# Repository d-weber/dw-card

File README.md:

# My business card

### Features:
- ESP32-S3
- 240x240 TFT LCD
- 8 Buttons
- Battery (CR2032) or USB-C Powered
- Cladd D Audio amp with 1W Speaker

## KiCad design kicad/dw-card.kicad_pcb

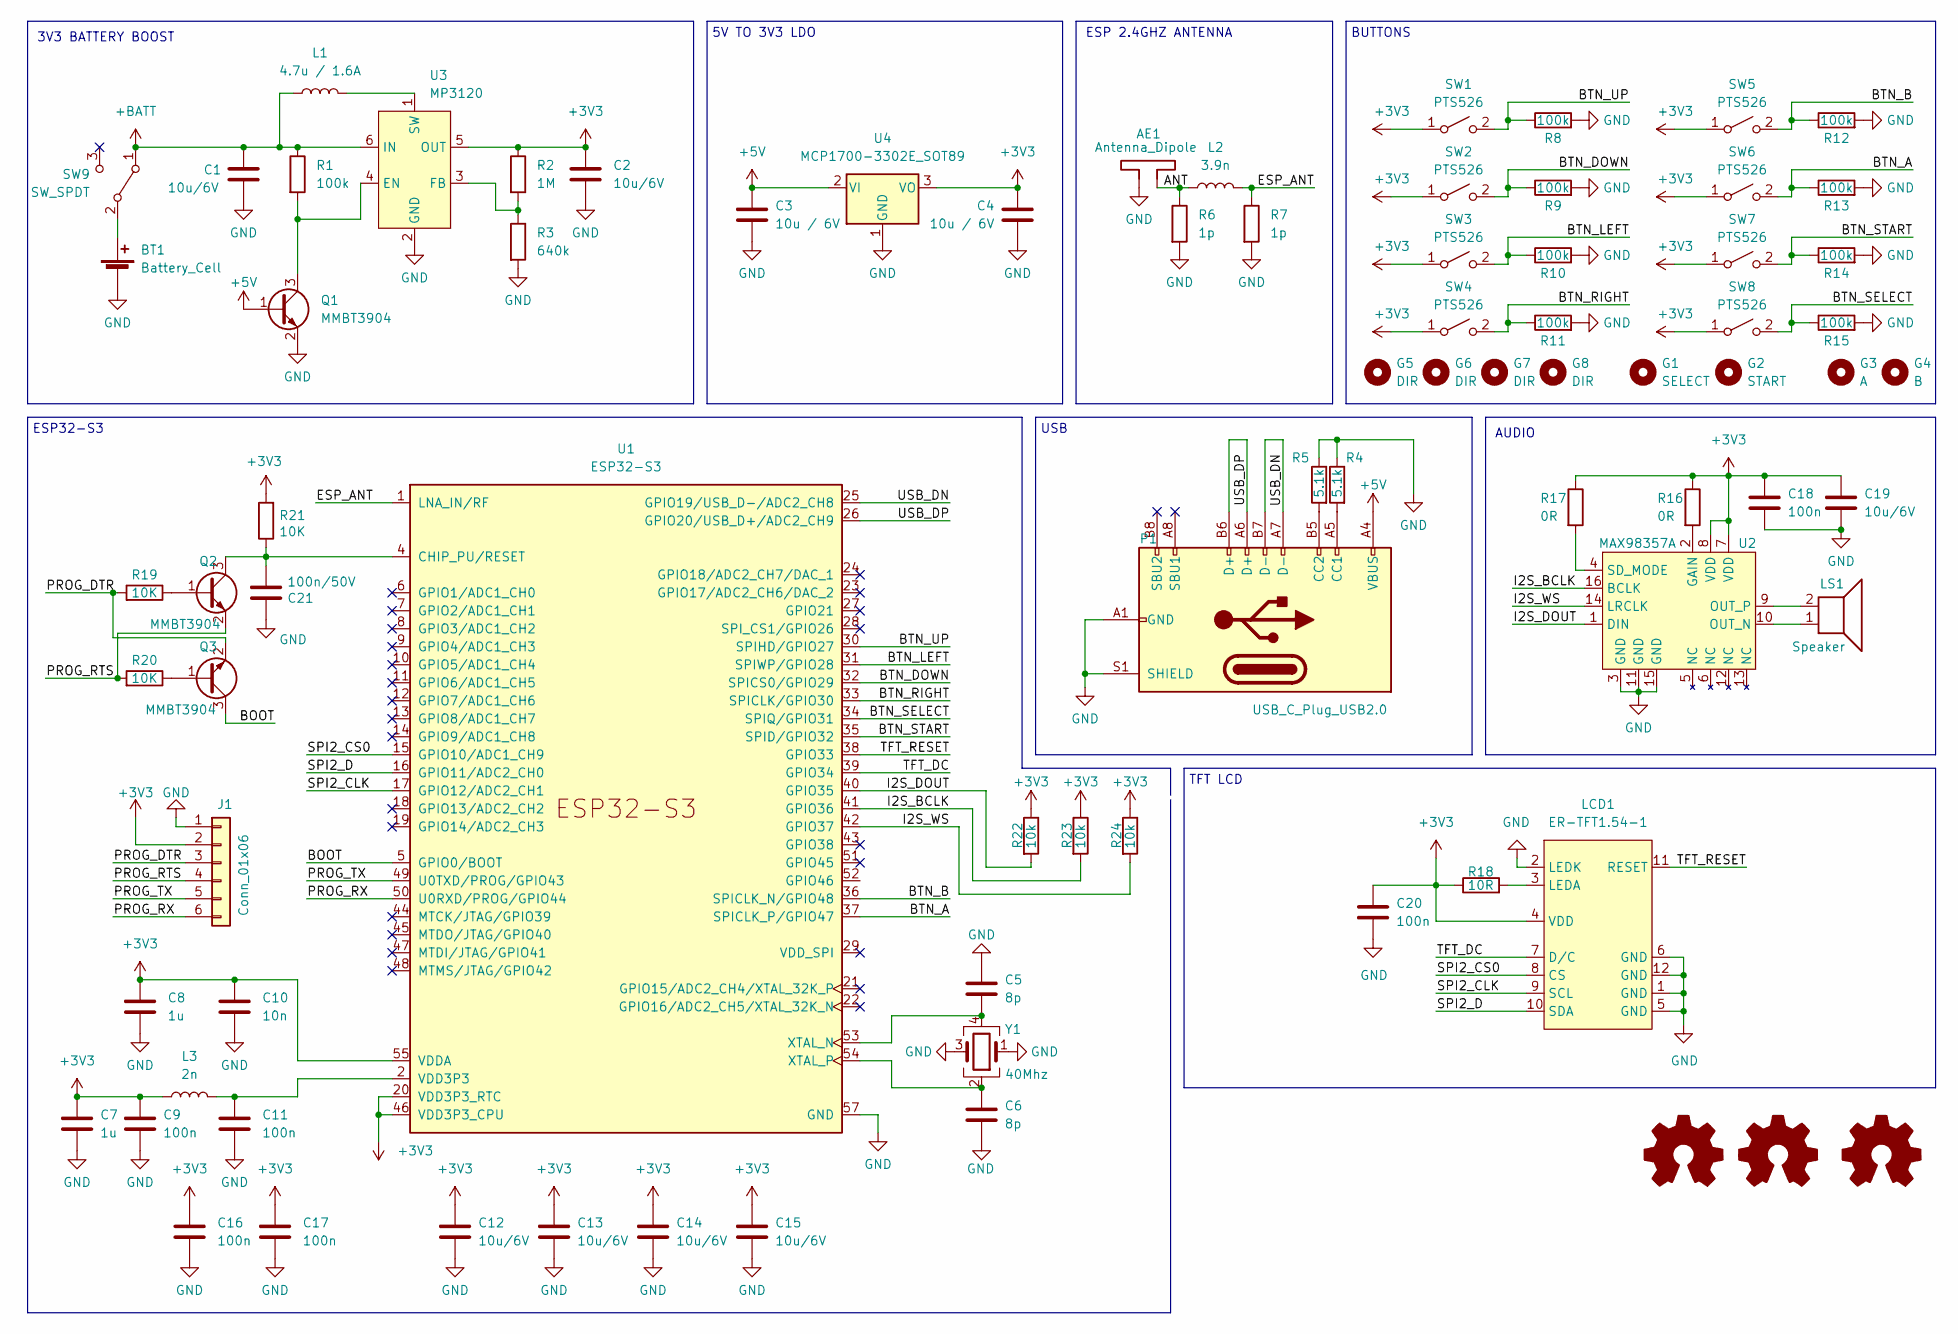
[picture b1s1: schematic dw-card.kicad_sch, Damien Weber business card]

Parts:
AE1: Antenna_Dipole; SWRA117D_Right
BT1: Battery_Cell; 2980
C1, C2, C12, C13, C14, C15, C19: 10u/6V; C_0805_2012Metric
C3, C4: 10u / 6V; C_0805_2012Metric
C5, C6: 8p; C_0603_1608Metric
C7, C8: 1u; C_0603_1608Metric
C9, C11, C16, C17, C18, C20: 100n; C_0603_1608Metric
C10: 10n; C_0603_1608Metric
C21: 100n/50V; C_0603_1608Metric
G1: SELECT; btn_select
G2: START; btn_start
G3: A; btn_a
G4: B; btn_b
G5, G6, G7, G8: DIR; btn_dir
J1: Conn_01x06; TC2030-MCP-NL
L1: 4.7u / 1.6A; L_Taiyo-Yuden_MD-3030
L2: 3.9n; L_0402_1005Metric
L3: 2n; L_0603_1608Metric
LCD1: ER-TFT1.54-1; ER-TFT-1.54
LDW1: Logo_Open_Hardware_Small; logo
LDW2: Logo_Open_Hardware_Small; logo_dw
LDW3: Logo_Open_Hardware_Small; qrcode_github
LS1: Speaker; CMS-15118D-SP
P1: USB_C_Plug_USB2.0; USB4510
Q1, Q2, Q3: MMBT3904; SOT-23
R1, R8, R9, R10, R11, R12, R13, R14, R15: 100k; R_0603_1608Metric
R2: 1M; R_0603_1608Metric
R3: 640k; R_0603_1608Metric
R4, R5: 5.1k; R_0603_1608Metric
R6, R7: 1p; R_0402_1005Metric
R16, R17: 0R; R_0603_1608Metric
R18: 10R; R_0603_1608Metric
R19, R20, R21: 10K; R_0603_1608Metric
R22, R23, R24: 10k; R_0603_1608Metric
SW1, SW2, SW3, SW4, SW5, SW6, SW7, SW8: PTS526
SW9: SW_SPDT; SW_SPDT_PCM12
U1: ESP32-S3; QFN-56-1EP_7x7mm_P0.4mm_EP5.6x5.6mm
U2: MAX98357A; TQFN-16-1EP_3x3mm_P0.5mm_EP1.23x1.23mm
U3: MP3120; TSOT-23-6
U4: MCP1700-3302E_SOT89; SOT-89-3
Y1: 40Mhz; Crystal_SMD_2016-4Pin_2.0x1.6mm

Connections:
+3V3: C2.1, C4.2, C7.1, C8.1, C9.1, C10.1, C12.1, C13.1, C14.1, C15.1, C16.1, C17.1, C18.1, C19.1, C20.1, J1.2, L3.1, LCD1.4 (VDD), R2.1, R16.1, R17.1, R18.1, R21.2, R22.1, R23.1, R24.1, SW1.1 (A), SW2.1 (A), SW3.1 (A), SW4.1 (A), SW5.1 (A), SW6.1 (A), SW7.1 (A), SW8.1 (A), U1.20 (VDD3P3_RTC), U1.46 (VDD3P3_CPU), U1.55 (VDDA), U1.56 (VDDA), U2.7 (VDD), U2.8 (VDD), U3.5 (OUT), U4.3 (VO)
+5V: C3.1, P1.A4 (VBUS), P1.A9 (VBUS), Q1.1 (B), U4.2 (VI)
+BATT: C1.1, L1.1, R1.1, SW9.1 (A), U3.6 (IN)
/ANT: AE1.1, L2.1, R6.1
/BOOT: Q3.3 (C), U1.5 (GPIO0/BOOT)
/BTN_A: R13.1, SW6.2 (B), U1.37 (SPICLK_P/GPIO47)
/BTN_B: R12.1, SW5.2 (B), U1.36 (SPICLK_N/GPIO48)
/BTN_DOWN: R9.1, SW2.2 (B), U1.32 (SPICS0/GPIO29)
/BTN_LEFT: R10.1, SW3.2 (B), U1.31 (SPIWP/GPIO28)
/BTN_RIGHT: R11.1, SW4.2 (B), U1.33 (SPICLK/GPIO30)
/BTN_SELECT: R15.1, SW8.2 (B), U1.34 (SPIQ/GPIO31)
/BTN_START: R14.1, SW7.2 (B), U1.35 (SPID/GPIO32)
/BTN_UP: R8.1, SW1.2 (B), U1.30 (SPIHD/GPIO27)
/ESP_ANT: L2.2, R7.1, U1.1 (LNA_IN/RF)
/I2S_BCLK: R23.2, U1.41 (GPIO36), U2.16 (BCLK)
/I2S_DOUT: R22.2, U1.40 (GPIO35), U2.1 (DIN)
/I2S_WS: R24.2, U1.42 (GPIO37), U2.14 (LRCLK)
/PROG_DTR: J1.3, Q3.2 (E), R19.2
/PROG_RTS: J1.4, Q2.2 (E), R20.2
/PROG_RX: J1.6, U1.50 (U0RXD/PROG/GPIO44)
/PROG_TX: J1.5, U1.49 (U0TXD/PROG/GPIO43)
/SPI2_CLK: LCD1.9 (SCL), U1.17 (GPIO12/ADC2_CH1)
/SPI2_CS0: LCD1.8 (CS), U1.15 (GPIO10/ADC1_CH9)
/SPI2_D: LCD1.10 (SDA), U1.16 (GPIO11/ADC2_CH0)
/TFT_DC: LCD1.7 (D/C), U1.39 (GPIO34)
/TFT_RESET: LCD1.11 (RESET), U1.38 (GPIO33)
/USB_DN: P1.A7 (D-), P1.B7 (D-), U1.25 (GPIO19/USB_D-/ADC2_CH8)
/USB_DP: P1.A6 (D+), P1.B6 (D+), U1.26 (GPIO20/USB_D+/ADC2_CH9)
GND: AE1.2, BT1.2 (-), C1.2, C2.2, C3.2, C4.1, C5.1, C6.2, C7.2, C8.2, C9.2, C10.2, C11.2, C12.2, C13.2, C14.2, C15.2, C16.2, C17.2, C18.2, C19.2, C20.2, C21.2, J1.1, LCD1.1 (GND), LCD1.2 (LEDK), LCD1.5 (GND), LCD1.6 (GND), LCD1.12 (GND), P1.A1 (GND), P1.A12 (GND), P1.S1 (SHIELD), Q1.2 (E), R3.2, R4.1, R5.1, R6.2, R7.2, R8.2, R9.2, R10.2, R11.2, R12.2, R13.2, R14.2, R15.2, U1.57 (GND), U2.3 (GND), U2.11 (GND), U2.15 (GND), U3.2 (GND), U4.1 (GND), Y1.1, Y1.3
unnamed: BT1.1 (+), SW9.2 (B)
unnamed: LCD1.3 (LEDA), R18.2
unnamed: P1.A5 (CC1), R4.2
unnamed: P1.B5 (CC2), R5.2
unnamed: Q1.3 (C), R1.2, U3.4 (EN)
unnamed: Q2.1 (B), R19.1
unnamed: C21.1, Q2.3 (C), R21.1, U1.4 (CHIP_PU/RESET)
unnamed: Q3.1 (B), R20.1
unnamed: C5.2, U1.53 (XTAL_N), Y1.4
unnamed: C6.1, U1.54 (XTAL_P), Y1.2
unnamed: R16.2, U2.2 (GAIN)
unnamed: LS1.1, U2.10 (OUT_N)
unnamed: LS1.2, U2.9 (OUT_P)
unnamed: R17.2, U2.4 (SD_MODE)
unnamed: R2.2, R3.1, U3.3 (FB)
unnamed: L1.2, U3.1 (SW)
VDD3P3: C11.1, L3.2, U1.2 (VDD3P3), U1.3 (VDD3P3)

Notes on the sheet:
ESP32-S3
BUTTONS
AUDIO
ESP 2.4GHZ ANTENNA
5V TO 3V3 LDO
TFT LCD
USB
3V3 BATTERY BOOST

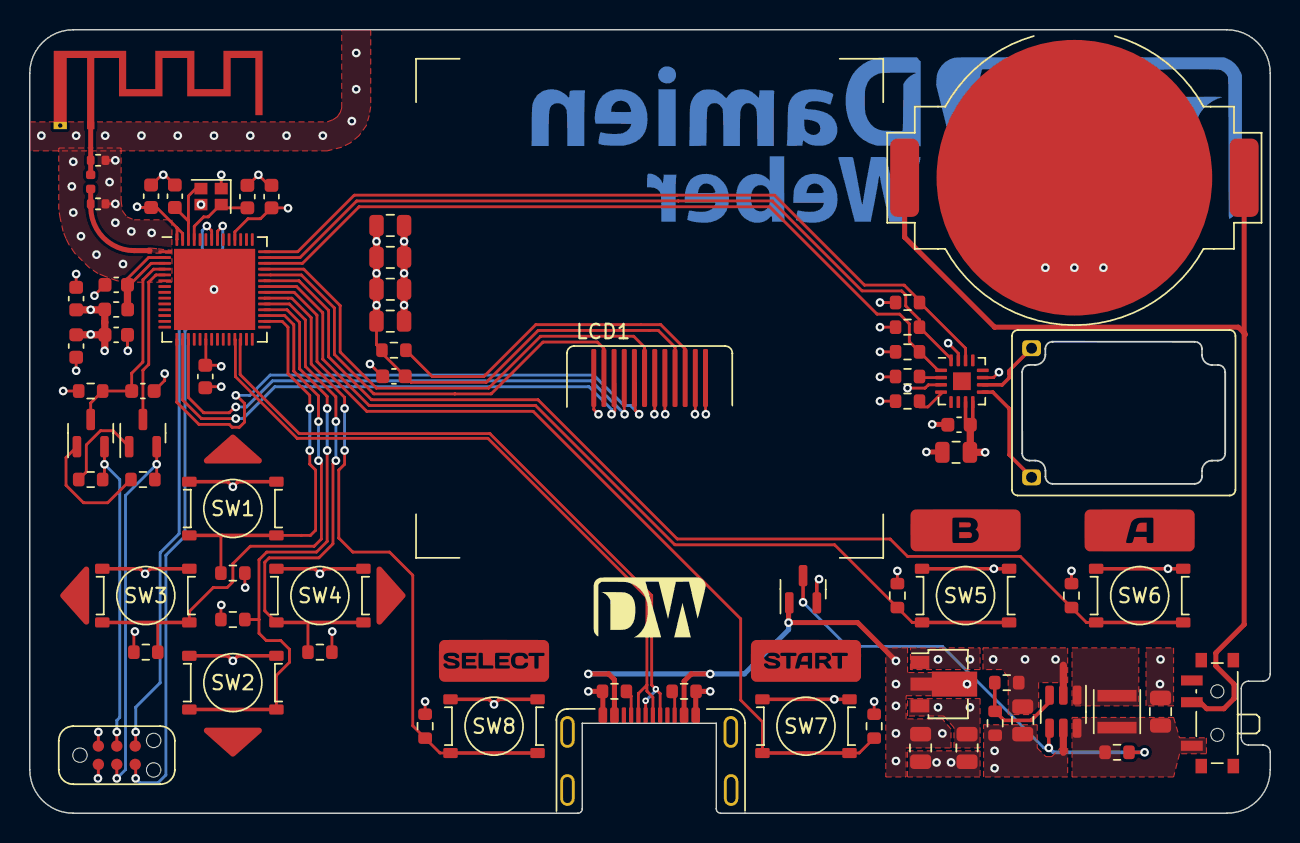
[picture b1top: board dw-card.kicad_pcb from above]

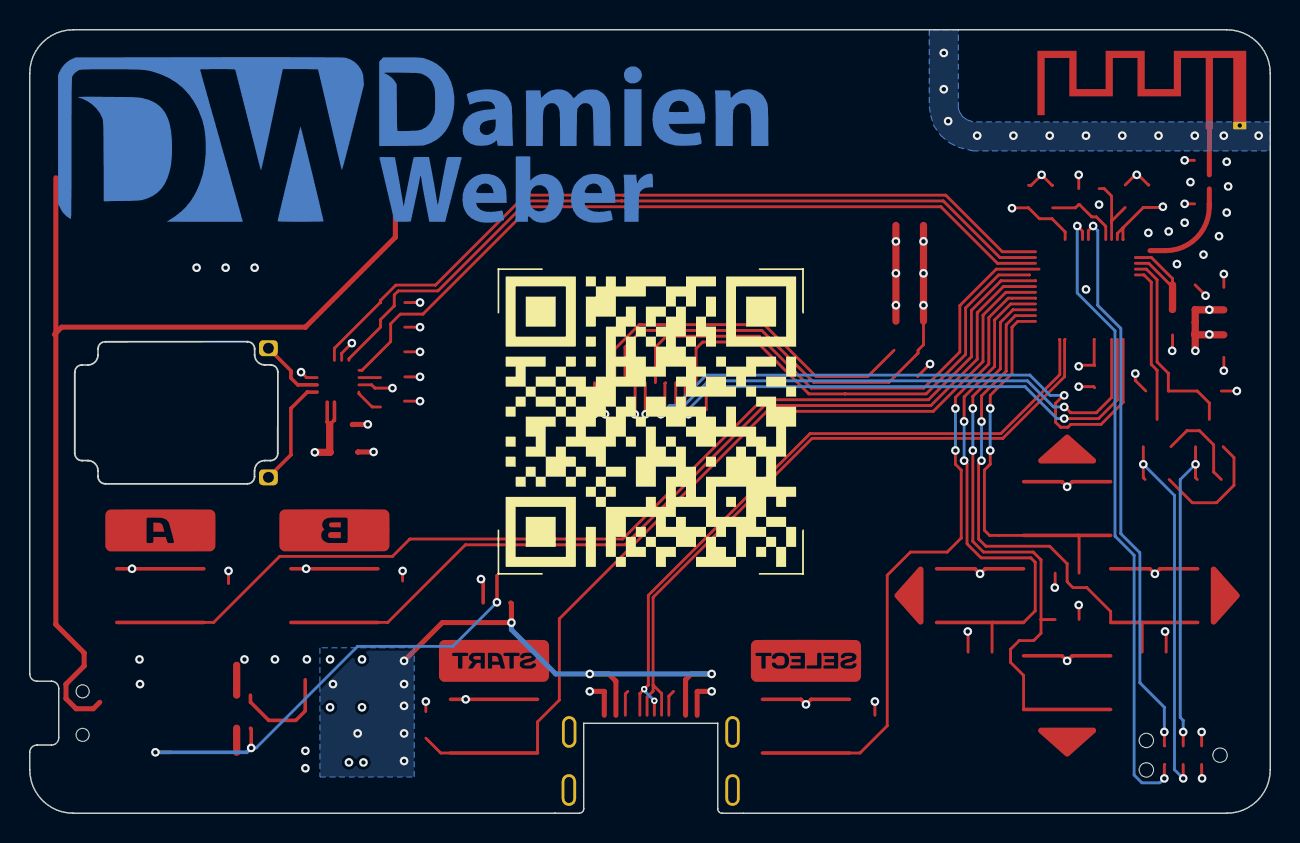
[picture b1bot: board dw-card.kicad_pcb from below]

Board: 4 copper layers, 85.5 x 54.0 mm, 82 parts (2 on the bottom side), 46 nets.

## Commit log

2023-02-26 add gh qrcode & readme
2023-02-26 invert A & B buttons
2023-03-01 fix pcb img
2023-03-02 update pcb image
